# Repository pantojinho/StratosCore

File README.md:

# StratosCore

StratosCore is an open-source portable field, aviation, meteorological, navigation and radio computer based on the **ESP32-S3-WROOM-1-N16R8**.

## Current status

**Astra has assumed full technical leadership of Rev A (2026-09-24).** Astra owns engineering closure, candidate refinement, review and integration; Claude, Hermes, Sol and other AI agents execute bounded delegated tasks. See [Astra project control and agent handover](docs/ASTRA_PROJECT_CONTROL.md) for current responsibilities, received evidence and next actions. Final baseline implementation and manufacturing remain gated.

| Complete | In progress | Externally blocked |
| --- | --- | --- |
| Product baseline and licensing | Validate prepared three-line display support and GNSS passive RF proposals | Display controlled power/FPC drawing, C1 samples and connector confirmation |
| MAX-M10S decision and independently reviewed footprint geometry | Close complete 2S charger/protection/VBUS application | Qualified electrical/battery review and fault tests |
| Two removable 21700 cells in 2S decision | Accept exact cells/holder and state estimation; prove the 8 h primary-use target | RF performance and runtime measurements need prototypes |
| ESP32 compute sheet and GPIO allocation | Sensor CAD, LoRa/ADS-B RF, stackup and mechanical dummy | Final factory stack confirmation |
| Exact candidates for RP2040 support, microSD, audio, USB-C, expansion, buttons, rails and RF interconnects | Assembler approvals, mechanical fit, off-state review and application tests | Independent final schematic/layout and bring-up review |
| Manufacturer-derived dimensions for W25Q, TPD, ICM/MMC/BMP, ABM8, U.FL and DM3 electrical/mechanical envelope | RF return paths, enclosure access and prototype qualification | PCBA assembler stencil/mask confirmation |
| KiCad hierarchy; latest ERC: zero violations | Orderable BOM and manufacturing inputs | |
| ADS-B host models: 24 tests passing | UART/PIO/DMA implementation and sustained-link bench proof | |

The **reviewed baseline** (`hardware/`) has no finished schematic, PCB layout, prototype or manufacturing package yet. A complete **comparison candidate** (schematic + routed PCB + 3D with the display) now exists in [`candidates/claude-oneshot-revA/`](candidates/claude-oneshot-revA/README.md) — see [below](#claude-one-shot-candidate-schematic--pcb--3d). It is **not for manufacture** and does not close any gate. Do not order boards from the current repository. See [project status](docs/PROJECT_STATUS.md) for the complete gate list.

## Claude one-shot candidate (schematic + PCB + 3D)

Generated 2026-09-23 at the owner's request, for side-by-side comparison with the Astra pass. Status at a glance:

| Item | Status |
| --- | --- |
| Schematic | Complete: root + 11 sheets, every Rev A block; unverified values are literally `TBD` |
| PCB | 60 x 84 mm, 4 layers, 277 parts, routed; **11 connections left for manual finish** (2 LoRa RF stubs, SHT40 SDA/3V3, 1 decoupling cap, 6 GND pour fragments) |
| Checks (KiCad 10.0.6) | ERC 1 reviewed error; DRC 1 reviewed error (ESP32 antenna-clearance courtyard); schematic <-> PCB parity 0 |
| 3D | Board with display, 2S 21700 cells and holder; printed two-part enclosure concept |
| Blocking gates | O05 battery safety (qualified human review), display controlled drawing/samples, LoRa matching values, ADS-B threshold, assembler approvals |
| Findings for the baseline | 2 footprint blockers (MMC5983MA, BMP581 pad centres), 2 wrong packages (TXU0202, TPS259474L), connector orientation and GPIO gaps — see [ISSUES.md](candidates/claude-oneshot-revA/docs/ISSUES.md) |

| Front (display) | Back (2S 21700 cells) | Printed enclosure concept |
| --- | --- | --- |
|  |  |  |

| PCB top (display removed) | PCB bottom | Copper (F/In2/B) |
| --- | --- | --- |
|  |  |  |

Schematic sheets (click to enlarge; full vector PDF: [schematic.pdf](candidates/claude-oneshot-revA/docs/schematic.pdf)):

| | | |
| --- | --- | --- |
|  Root |  01 USB-C input |  02 2S battery/charger |
|  03 Rails |  04 ESP32 / control |  05 Display / touch |
|  06 Sensors |  07 GNSS |  08 LoRa |
|  09 ADS-B / RP2040 |  10 microSD / audio |  11 Mechanical |

### Open it in KiCad

1. Download the repository (GitHub **Code -> Download ZIP**, or `git clone`) and install **KiCad 10** (the project uses the KiCad 10 library variables).
2. Open [`candidates/claude-oneshot-revA/kicad/StratosCore_Claude.kicad_pro`](candidates/claude-oneshot-revA/kicad/). Project symbols, footprints and 3D models are local to that folder (`libs/`), so no library setup is needed.
3. Schematic: open the root sheet and double-click a sheet box. PCB: open the board and press **Alt+3** for the 3D viewer (the display and the cells appear in 3D).
4. STEP files for FreeCAD, Fusion or any other CAD are in [`candidates/claude-oneshot-revA/outputs/StratosCore_Claude_3D_STEP.zip`](candidates/claude-oneshot-revA/outputs/StratosCore_Claude_3D_STEP.zip): the board with its display and cells, the full assembly with the enclosure, and the two enclosure parts.

| Folder | What to open |
| --- | --- |
| `candidates/claude-oneshot-revA/kicad/` | KiCad project (`.kicad_pro`, root and sheet `.kicad_sch`, `.kicad_pcb`, local libraries) |
| `candidates/claude-oneshot-revA/docs/` | `schematic.pdf`, `ISSUES.md` (findings and open gates) |
| `candidates/claude-oneshot-revA/outputs/` | STEP zip, renders, layer PDF, BOM, DRC summary, netlist |
| `candidates/claude-oneshot-revA/mech/` | Enclosure STEP parts |
| `candidates/claude-oneshot-revA/images/` | The images above |
| `candidates/claude-oneshot-revA/tools/` | Scripts that regenerate everything |

The owner set a five-unit target of at most BRL 200 per assembled PCB **including display/touch**, excluding locally bought cells and enclosure, freight and taxes. This is a hobby prototype for desk, car and protected but unpressurized aircraft-cabin use, with experimental drone, model-aircraft, balloon, ultralight, hang-glider and paramotor applications to assess separately. About 10,000 ft is the realistic altitude case; 30,000 ft is exploratory, not a guaranteed barometric limit. The BMP581 remains an indicative backup sensor, and the 8 h minimum target on two 21700 cells remains. The five boards will be programmed and tested locally through USB-C. Cost, runtime and flight performance are not yet verified.

## Rev A baseline

| Block | Baseline |
| --- | --- |
| Compute | ESP32-S3-WROOM-1-N16R8; 16 MB Flash, 8 MB PSRAM; Wi-Fi/BLE and module PCB antenna |
| User interface | 2.8-inch IPS 320 x 240 with capacitive touch; portrait/landscape; two physical buttons |
| GNSS | u-blox MAX-M10S-00B, selected for documented airborne modes to 80 km |
| Motion/environment | ICM-42688-P, MMC5983MA, BMP581 and SHT40-AD1B-R2 |
| LoRa | SX1262 directly integrated, 915 MHz class hardware, SPI and PCB U.FL; regional TX configuration required |
| ADS-B | Independent 1090 MHz receive chain with RP2040 timing processor |
| Logging/audio | Mandatory microSD and provision for an optional digital MEMS microphone |
| Power | USB-C target; two removable matched 21700 cells in 2S; one balanced charger and common protection direction |
| Expansion | 3V3, GND, I2C, SPI with separate CS, UART and GPIO/IRQ |
| Construction | Four-layer PCB; 84 x 60 mm planning outline; approximately 88 x 64 x 37 mm printed enclosure starting envelope |

Potential uses include flight/vario instruments, traffic visualization, balloon experiments, weather stations, trackers, LoRa/MeshCore experiments and portable logging. This experimental platform is not a certified aviation instrument, collision-avoidance system or cockpit voice recorder.

## Start here

1. [Project status: completed work and remaining gates](docs/PROJECT_STATUS.md)
2. [Astra-led engineering workboard](docs/PRE_ASTRA_WORKBOARD.md)
3. [Multi-agent swarm protocol and master prompt](docs/SWARM_PROTOCOL.md)
4. [Engineering documentation index](docs/README.md)
5. [Locked decisions and accepted proposals](docs/DECISIONS.md)
6. [Open engineering questions](docs/OPEN_QUESTIONS.md)

[Astra final KiCad handoff](docs/ASTRA_HANDOFF.md) is intentionally marked **NOT READY**. It is not the current work queue.

## Repository layout

```text
StratosCore/
|-- AGENTS.md          Engineering and review rules
|-- README.md          Public project status and entry points
|-- docs/              Status, decisions and subsystem specifications
|-- bom/               Preliminary planning BOM; not orderable yet
|-- hardware/          KiCad project and primary-source index
|-- candidates/        Out-of-baseline design candidates (Claude one-shot: schematic, PCB, 3D)
|-- mechanical/        Enclosure and fit-study workspace
|-- manufacturing/     Release and production-test placeholders
|-- firmware/          Hardware-interface fixtures and future firmware
|-- references/        Read-only research and reuse/license records
`-- LICENSES/          Official license texts and scope
```

## Manufacturing path

The target is four-layer PCB fabrication and automated assembly at JLCPCB or a comparable Chinese PCBA supplier. Release requires an independently reviewed schematic and layout, clean ERC/DRC, confirmed stackup, exact orderable BOM, CPL, Gerbers/drill files, assembly drawings and a programming/production-test procedure. The owner must explicitly accept the manufacturing release before ordering.

## Licensing

Original hardware, mechanical designs and hardware engineering documentation use **CERN-OHL-P-2.0**. Original firmware and its software documentation use **MIT**. See [license scope and provenance](LICENSES/README.md). Third-party work retains its own terms.

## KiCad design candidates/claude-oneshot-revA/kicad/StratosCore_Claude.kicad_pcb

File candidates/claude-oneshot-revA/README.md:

# StratosCore Rev A — Claude one-shot candidate (schematic + PCB + 3D)

> **Status: CANDIDATE FOR COMPARISON — NOT FOR MANUFACTURE, NOT A BASELINE.**
>
> **2026-09-24 project control:** Astra has assumed full technical leadership, review and integration. Claude, Hermes, Sol and other agents execute bounded delegated tasks. See [Astra project control and handover](../../docs/ASTRA_PROJECT_CONTROL.md) for received results, discrepancies and T1–T8. Candidate GPIO/mask decisions remain subject to implementation and validation; root safety, budget and release gates remain in force.
> Produced 2026-09-23 at the owner's explicit request ("1 shot" schematic, PCB and 3D with the display) to be compared with the GPT Astra pass. `docs/ASTRA_HANDOFF.md` is still **NOT READY**; nothing here closes a gate in `docs/PROJECT_STATUS.md`. Battery safety (O05) needs a qualified human reviewer — **do not energize this design with cells.** The repository baseline in `hardware/` is untouched.
>
> **2026-09-23 refinement:** evidence-backed corrections were applied inside this folder (TXU0202 exact DCU land, TPS259474L RPW stencil/fab, ICM-42688-P pin 9 to GND, U1/J5 courtyard, duplicate vias, BMP581 under-body SCL route, SHT40 SDA, 3V3 fragments, three GND islands, silkscreen). See [docs/REFINEMENT_2026_09_23.md](docs/REFINEMENT_2026_09_23.md) for evidence, before/after reports and the blockers that remain.
>
> **2026-09-23 GND stitch (Hermes, evening):** three floating GND pads (U2 USB-ESD, U3.8 eFuse, U24.2 TXU0202) were reported connected to the In1 plane — `unconnected` down to 2 (LoRa TBD items). U7 land updated to RGT0016C. See [docs/GND_STITCH_2026_09_23.md](docs/GND_STITCH_2026_09_23.md). The 10 U3 clearance findings remain electrical defects requiring resolution, not cosmetic findings or fabrication acceptance.

| Front (display) | Back (2S 21700 cells) | PCB top | Enclosure concept |
| --- | --- | --- | --- |
|  |  |  |  |

All 12 schematic sheets are in [`images/`](images/) as PNG (`schematic_00_root.png` ... `schematic_11_mechanical.png`) and in [`docs/schematic.pdf`](docs/schematic.pdf).

## Open it in KiCad

1. Install **KiCad 10** and download/clone the repository.
2. Open `kicad/StratosCore_Claude.kicad_pro`. Symbols, footprints and 3D models used by the project live in `kicad/libs/` (`SC.kicad_sym`, `SC.pretty`, `SC.3dshapes`) and are referenced through `${KIPRJMOD}`; standard KiCad parts come from the KiCad 10 install.
3. Schematic: root sheet -> double-click a sheet box. PCB: open the board, **Alt+3** for the 3D view (display envelope 5 mm above the board, 2S cells below).
4. Other CAD tools: unzip `outputs/StratosCore_Claude_3D_STEP.zip` (board + display + cells, full assembly with enclosure, enclosure parts).

## What is in this folder

| Path | Content |
| --- | --- |
| `kicad/StratosCore_Claude.kicad_pro/.kicad_sch/.kicad_pcb` | KiCad 10.0.6 project: root + 11 hierarchical sheets, 4-layer 60 x 84 mm board |
| `kicad/libs/SC.kicad_sym`, `SC.pretty`, `SC.3dshapes` | Project symbols (datasheet pin tables), footprints (repo candidates + generated/corrected ones), STEP envelopes |
| `kicad/reports/` | Current ERC/DRC JSON and netlist, dated `before_2026-09-23/` and `after_2026-09-23/` sets with net/pad reconciliation, unassigned-pin report (pre-refinement) |
| `docs/schematic.pdf` | Schematic, 12 pages |
| `docs/ISSUES.md` | **Findings against the repo baseline (incl. 2 footprint blockers), open gates, layout limitations** |
| `docs/REFINEMENT_2026_09_23.md` | Refinement record: preflight, evidence per correction, before/after checks, dispositions, blockers |
| `outputs/` | Renders (top/bottom/iso), `StratosCore_Claude_3D_STEP.zip` (board STEP with display + 2S cells, full assembly STEP with the enclosure, enclosure parts), assembly SVG views, layer PDF, BOM, review-only positions, DRC summary |
| `mech/` | Printed enclosure concept (front bezel with display window, back shell) |
| `images/` | README images: 3D renders, enclosure views, copper layers, all schematic sheets |
| `tools/` | Reproducible generators: `design.py` (circuit), `build_sch.py`, `build_pcb.py`, `models3d.py`, `assemble.py`, `export.py` |

## Design summary

- **Compute:** ESP32-S3-WROOM-1-N16R8, GPIO map exactly as `docs/INTERFACE_GPIO_MAP.md`; antenna at the left board edge.
- **Power:** USB-C (USB4105) -> TPD4E05U06 -> TPS259474L eFuse (PWR-02 values) -> BQ25887 balanced 2S charger (TI Fig. 69 values, fail-safe CD) -> removable 2S 21700 holder -> S-8252-family protection placeholder (O05) -> TPS62130A 3V3_MAIN; TPS7A2030 quiet 3.0 V (ADS-B), TPS7A2018 1.8 V; three TPS22918 switched domains (SD, ADS-B digital, audio).
- **Display:** Orient AFY240320A1-2.8INTH-C1 on XF3M-4015/0615 FPC connectors, SN74AXC4T245 3.3->1.8 V write-only 3-line SPI, SN74LVC1G07 reset, TPS61169 backlight (2.21 ohm, ~92 mA). Modelled 5 mm above the PCB on a printed frame.
- **Sensors:** ICM-42688-P, MMC5983MA, BMP581 (vent edge, no copper under body), SHT40 on a slotted thermal tab.
- **Radios:** MAX-M10S-00B GNSS (passive antenna U.FL + TPD1E0B04), SX1262 + PE4259 (topology only, all RF values TBD), ADS-B chain BLB01 -> TA2003A -> BLB01 -> TA2003A -> ADL5513 -> MCP6566 -> RP2040 (+ W25Q128JVSIQ, ABM8-272-T3).
- **Other:** DM3AT microSD on switched 3V3_SD, T5838 PDM mic via TXU0202 on 1V8_AUDIO_SW, TCA9535 slow control, JST GH 12-pin expansion (board back), two SKSCLCE010 side buttons, test pads for rails/SWD/RUN/USB_BOOT/buses.

Every value that is not closed by a cited source is literally `TBD` in the schematic (value or `Status` field); see the BOM `Status` column.

## Verification status (KiCad 10.0.6; ERC/DRC rechecked 2026-09-24)

Records: [docs/REFINEMENT_2026_09_23.md](docs/REFINEMENT_2026_09_23.md) and the follow-up notes in [docs/review_notes/](docs/review_notes/). KiCad reports at most 199 items per violation type, so 199 is a lower bound.

[Astra's September 24 review](../../docs/ASTRA_AGENT_REVIEW_2026_09_24.md) independently reran ERC/DRC with zone refill. Other dimensional, physical and functional claims below retain their original evidence dates and limits.

| Check | Result |
| --- | --- |
| ERC (12 sheets) | 1 error (intended: BMP581 `INT` strapped to GND with `INT_CONFIG.int_en` kept disabled, Bosch DS004-13 Table 28/§6.2) + 5 warnings (intended GND straps; flattened `2N7002` symbol) |
| Schematic <-> PCB parity / net-pad reconciliation | **0** / 970 pins, 0 mismatches (correspondence only) |
| GND copper | one connected group (U2 USB ESD, U3 eFuse, U24, U7 buck EP and the sensor islands are now stitched) |
| DRC errors | **209 reported: 10 clearance + 199 mask bridges**, plus 2 unconnected items listed separately. Mask count is a lower bound; clearance and mask/routing defects remain open. See [Astra's fresh review](../../docs/ASTRA_AGENT_REVIEW_2026_09_24.md) and [assembler note](docs/review_notes/ASSEMBLER_MASK_AND_COST_SNAPSHOT.md) |
| DRC warnings | 118 silkscreen (cosmetic) + 1 dangling LoRa RF stub |
| Unconnected | **2**: SX1262 `LORA_RFO`/`LORA_RFI_P`, the intended RF blocker ([E449 reference values](docs/review_notes/SX1262_E449_REFERENCE_VALUES.md) found; the `08_lora` topology must first be redrawn to E449) |
| ESP32 / USB-C / buttons | All 41 module pads traced to Espressif Table 3-1 and the GPIO map; USB-C on the bottom (PWR) edge and buttons on the right edge, both facing out — see [audit](docs/review_notes/ESP32_USB_BUTTONS_AUDIT.md) for the open antenna/display and enclosure items |

Routing: Freerouting 2.4.1 (40 passes) on an engineering-anchored placement (`tools/build_pcb.py`), then this package's A* clean-up router (`tools/gridroute.py`), automated GND via stitching (`tools/finalize.py`) and polish (`tools/polish.py`); `tools/route_all.py` chains the stages. **A low DRC count proves CAD consistency only — not RF, power, battery-safety, thermal, EMI or manufacturability.** RF paths and USB were not given controlled-impedance geometry.

## How to regenerate

> The generators below produced the original one-shot. They do **not** include the 2026-09-23 refinement; re-running them would revert it. The KiCad files are now the source of truth; the refinement scripts are `tools/refine_2026_09_23_*.py` and `tools/fp_rpw_dcu_2026_09_23.py`. `outputs/StratosCore_Claude_3D_STEP.zip` is the ORIGINAL pre-refinement export (kept for history). Current-state models: `outputs/StratosCore_Claude_board_2026-09-23.step(.zip)` (board STEP, post-GND-stitch) and `outputs/positions_REVIEW_ONLY.csv` (re-exported from the current board).

```bash
"C:/Program Files/KiCad/10.0/bin/python.exe" tools/build_sch.py
```
```bash
"C:/Program Files/KiCad/10.0/bin/python.exe" tools/build_pcb.py
```
```bash
<python-with-cadquery> tools/models3d.py
```
```bash
"C:/Program Files/KiCad/10.0/bin/python.exe" tools/route_all.py --passes 40
```
```bash
"C:/Program Files/KiCad/10.0/bin/python.exe" tools/export.py
```
```bash
<python-with-cadquery> tools/assemble.py
```

STEP outputs are written to `outputs/` and committed zipped (`StratosCore_Claude_3D_STEP.zip`). Routing uses Freerouting 2.4.1 (`freerouting-2.4.1.jar`, GPL-3.0, run as an external tool only — not bundled) on an Eclipse Temurin 25 JRE; set `STRATOS_TOOLS` to the folder holding both.

## Tool provenance and licensing

- Hardware files: CERN-OHL-P-2.0 (repository policy). Generator scripts: MIT (tooling, not firmware).
- `tools/schgen.py` adapts ideas (coordinate transform, `extends` flattening, stub/label drawing) from [pantojinho/hermes-kicad-pcb](https://github.com/pantojinho/hermes-kicad-pcb) `sch_gen.py`, MIT, commit `c87e8d4`; the KiCad pitfalls list and board-from-netlist flow of `sch_to_board.py` informed `build_pcb.py`. [aklofas/kicad-happy](https://github.com/aklofas/kicad-happy) (MIT) was consulted as the review-skill reference; none of its code is included.
- KiCad library symbols/footprints/3D models are used under the KiCad libraries' license (CC-BY-SA 4.0 with the design exception).
- Datasheet facts used for new symbols/footprints are cited in each symbol `Datasheet` field / footprint `descr` and in `docs/ISSUES.md`.

## Suggested Astra comparison checklist

1. Did the other pass catch **A13 (MMC5983MA pad centres)** and **A14 (BMP581 pad centres)**, **A1/A2 (TXU0202 / TPS259474L wrong packages)** and **A3 (BM12B is vertical)**?
2. How were the GPIO gaps (A5-A8: EXP_CS, SX1262 NRESET, RP2040 RUN, touch reset) resolved?
3. Placement: antenna vs 2S holder (A16), holder vs mounting holes/THT (A15), sensor placement rules (SNS-02), RF chain adjacency.
4. Did it invent LoRa matching values, ADS-B threshold, charger/protection parts or display pin ties, or leave them TBD?
5. Routing quality of RF (GCPW), USB (90 ohm pair), buck/charger hot loops — neither pass should be trusted without hand review.

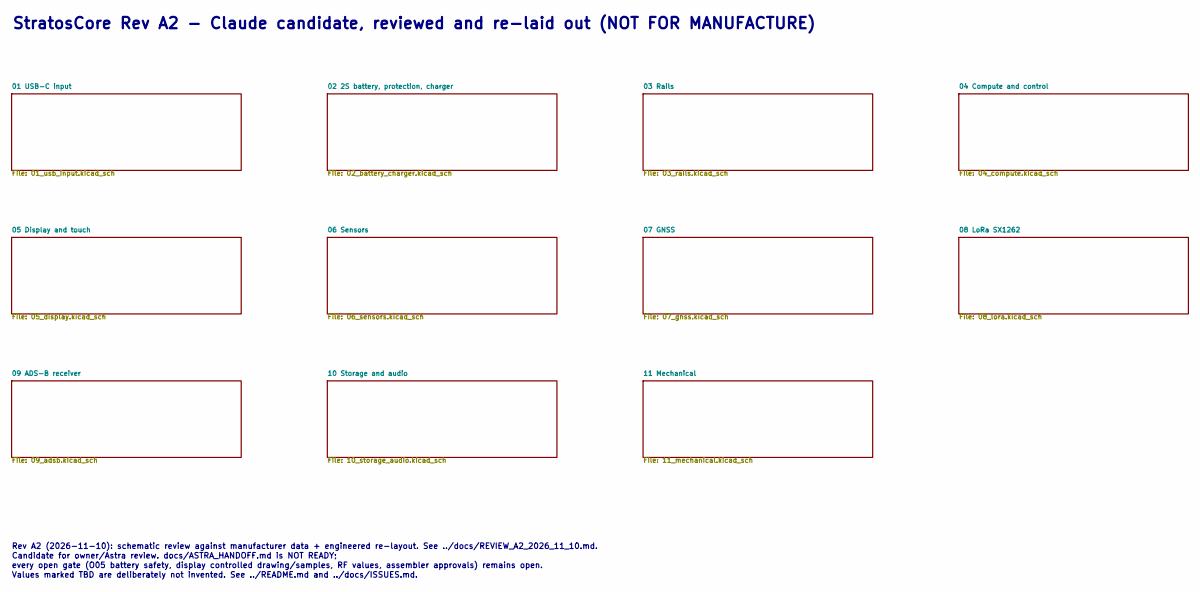
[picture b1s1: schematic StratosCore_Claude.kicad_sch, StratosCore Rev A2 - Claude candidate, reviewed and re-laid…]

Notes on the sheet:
StratosCore Rev A2 - Claude candidate, reviewed and re-laid out (NOT FOR MANUFACTURE)
Rev A2 (2026-11-10): schematic review against manufacturer data + engineered re-layout. See ../docs/REVIEW_A2_2026_11_10.md.
Candidate for owner/Astra review. docs/ASTRA_HANDOFF.md is NOT READY;
every open gate (O05 battery safety, display controlled drawing/samples, RF values, assembler approvals) remains open.
Values marked TBD are deliberately not invented. See ../README.md and ../docs/ISSUES.md.

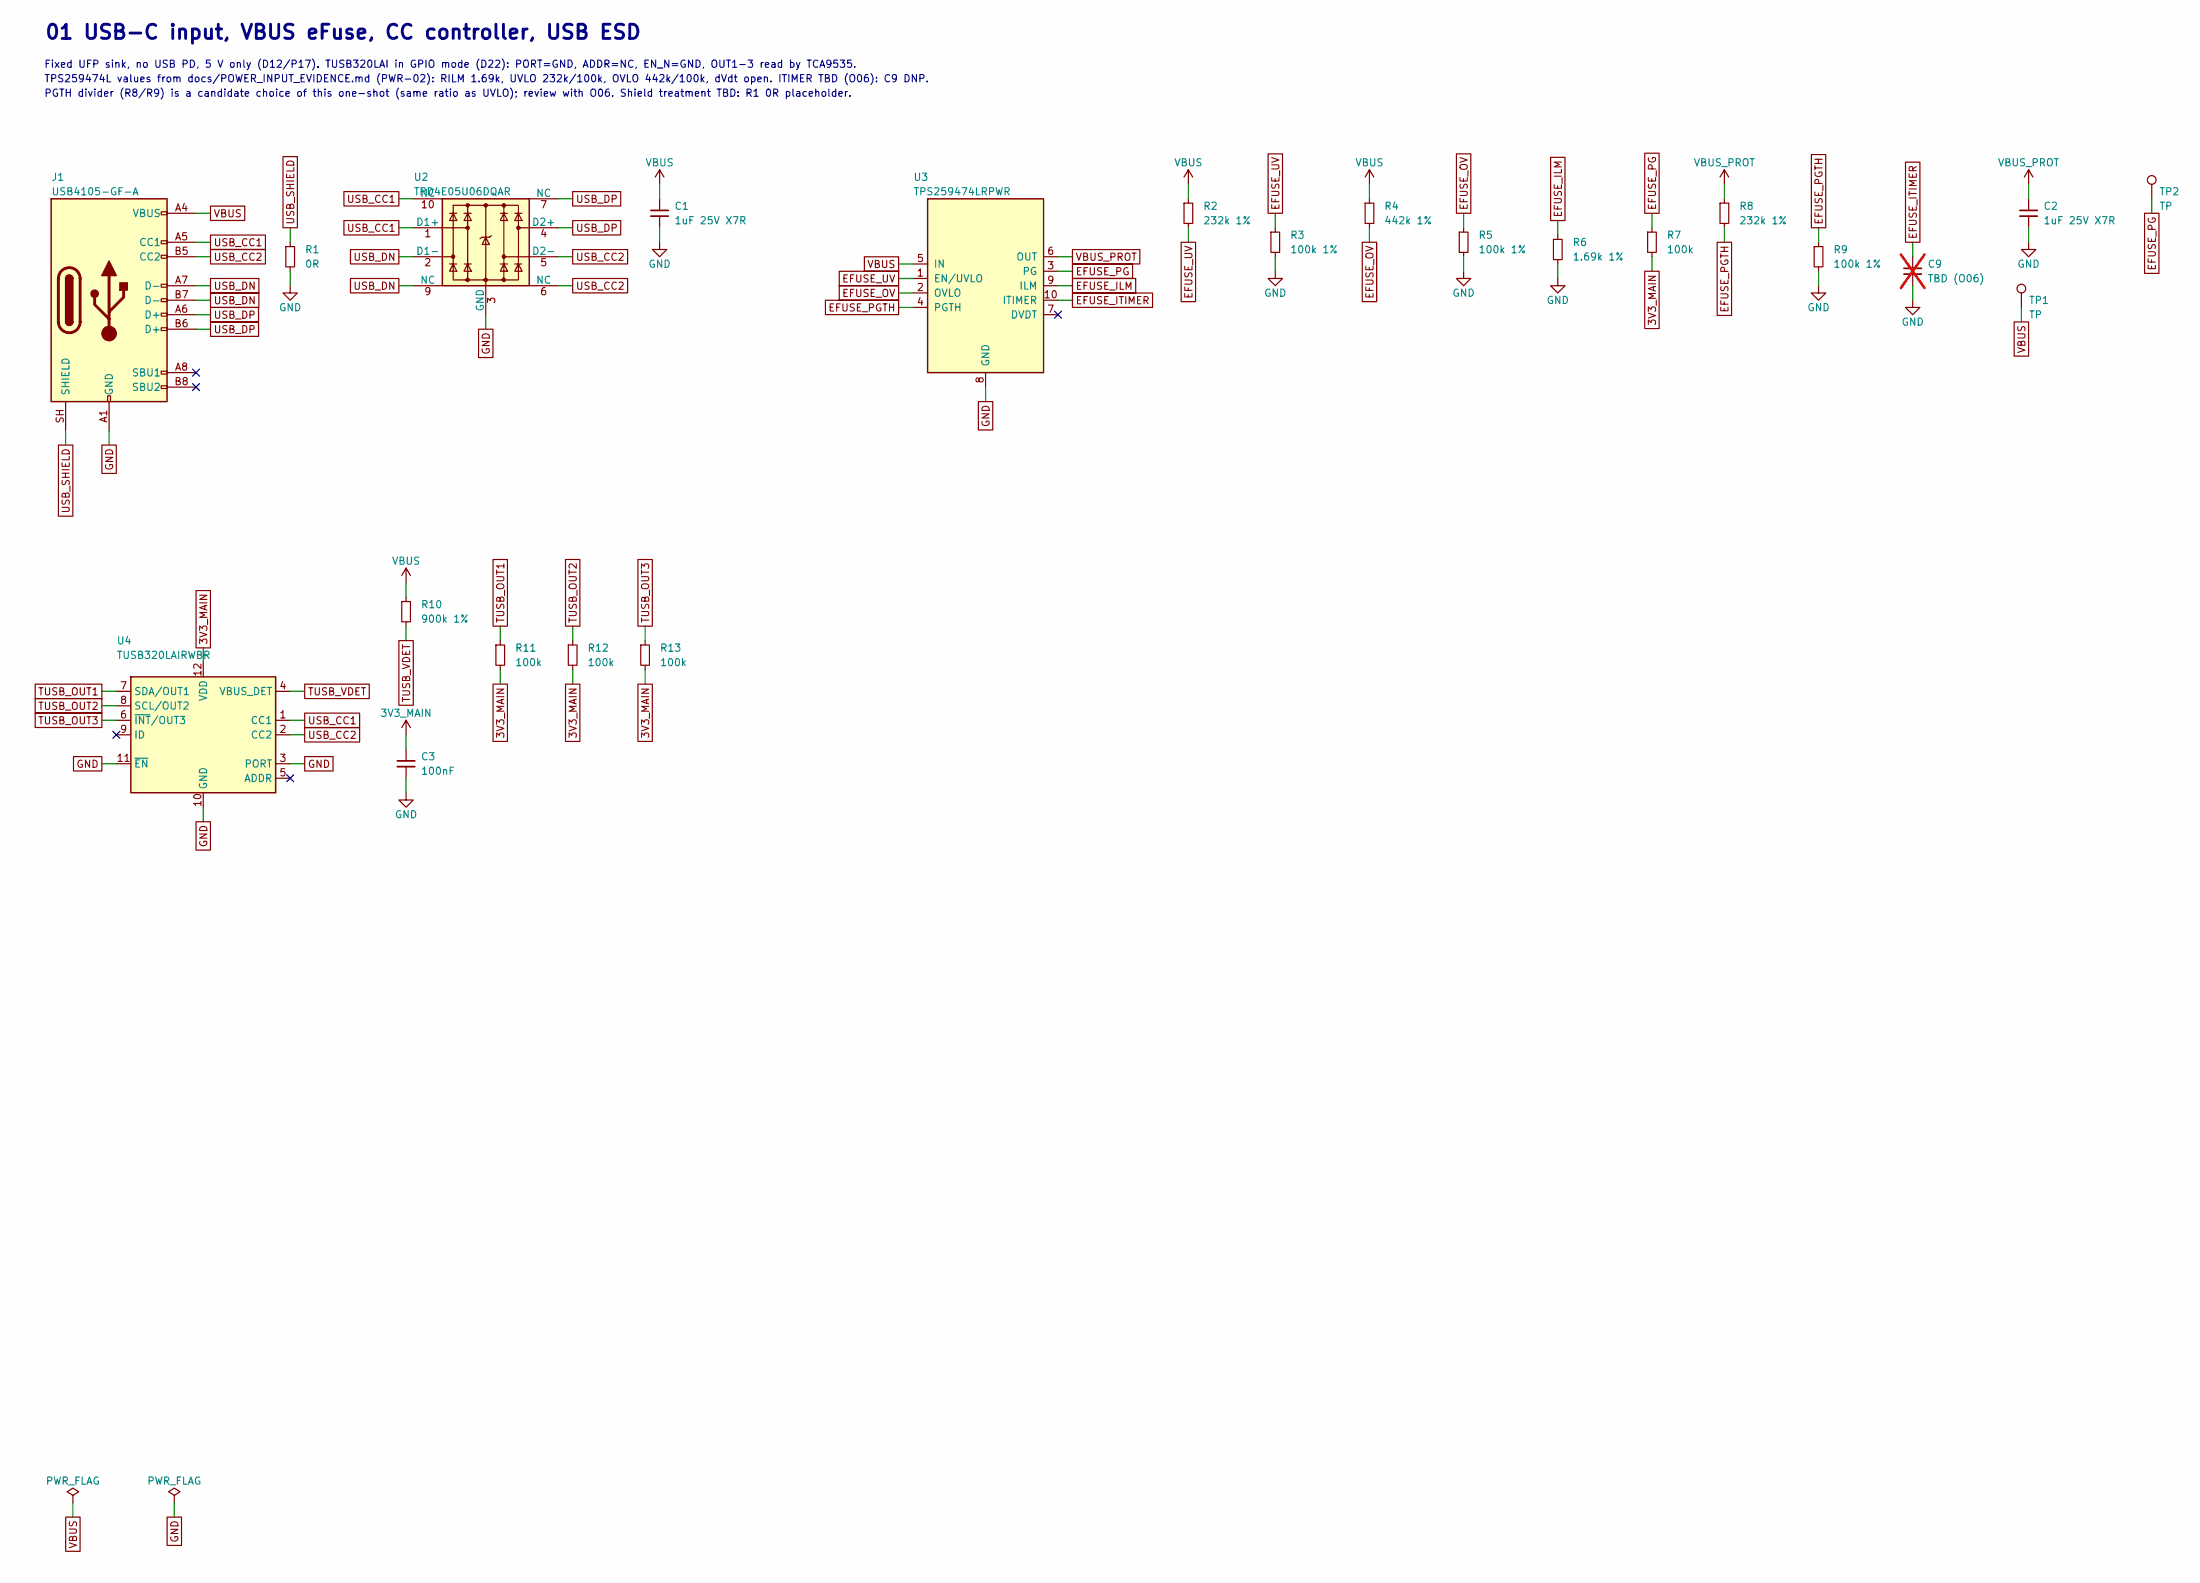
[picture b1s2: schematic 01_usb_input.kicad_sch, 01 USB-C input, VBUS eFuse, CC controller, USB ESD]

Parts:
C1, C2: 1uF 25V X7R; C_0603_1608Metric
C3: 100nF; C_0402_1005Metric
C9: TBD (O06); C_0402_1005Metric; not fitted
J1: USB4105-GF-A; USB_C_Receptacle_GCT_USB4105-xx-A_16P_TopMnt_Horizontal; MPN USB4105-GF-A
R1: 0R; R_0402_1005Metric
R2, R8: 232k 1%; R_0402_1005Metric
R3, R5, R9: 100k 1%; R_0402_1005Metric
R4: 442k 1%; R_0402_1005Metric
R6: 1.69k 1%; R_0402_1005Metric
R7, R11, R12, R13: 100k; R_0402_1005Metric
R10: 900k 1%; R_0402_1005Metric
TP1, TP2: TP; TestPoint_Pad_D1.0mm
U2: TPD4E05U06DQAR; USON-10_2.5x1.0mm_P0.5mm; MPN TPD4E05U06DQARG4
U3: TPS259474LRPWR; TI_RPW0010A_VQFN-HR-10_2x2mm_P0.45mm; MPN TPS259474LRPWR
U4: TUSB320LAIRWBR; TI_RWB0012B_X2QFN-12_1.6x1.6mm_TUSB320LAI; MPN TUSB320LAIRWBR

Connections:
3V3_MAIN: C3.1, R7.2, R11.2, R12.2, R13.2, U4.12 (VDD); also elsewhere on the board
EFUSE_ILM: R6.1, U3.9 (ILM)
EFUSE_ITIMER: C9.1, U3.10 (ITIMER)
EFUSE_OV: R4.2, R5.1, U3.2 (OVLO)
EFUSE_PG: R7.1, TP2.1, U3.3 (PG)
EFUSE_PGTH: R8.2, R9.1, U3.4 (PGTH)
EFUSE_UV: R2.2, R3.1, U3.1 (EN/UVLO)
GND: C1.2, C2.2, C3.2, C9.2, J1.A1 (GND), J1.A12 (GND), J1.B1 (GND), J1.B12 (GND), R1.2, R3.2, R5.2, R6.2, R9.2, U2.3 (GND), U2.8 (GND), U3.8 (GND), U4.3 (PORT), U4.10 (GND), U4.11 (~EN); also elsewhere on the board
TUSB_OUT1: R11.1, U4.7 (SDA/OUT1); also elsewhere on the board
TUSB_OUT2: R12.1, U4.8 (SCL/OUT2); also elsewhere on the board
TUSB_OUT3: R13.1, U4.6 (~INT/OUT3); also elsewhere on the board
TUSB_VDET: R10.2, U4.4 (VBUS_DET)
USB_CC1: J1.A5 (CC1), U2.1 (D1+), U2.10 (NC), U4.1 (CC1)
USB_CC2: J1.B5 (CC2), U2.5 (D2-), U2.6 (NC), U4.2 (CC2)
USB_DN: J1.A7 (D-), J1.B7 (D-), U2.2 (D1-), U2.9 (NC); also elsewhere on the board
USB_DP: J1.A6 (D+), J1.B6 (D+), U2.4 (D2+), U2.7 (NC); also elsewhere on the board
USB_SHIELD: J1.SH (SHIELD), R1.1
VBUS: C1.1, J1.A4 (VBUS), J1.A9 (VBUS), J1.B4 (VBUS), J1.B9 (VBUS), R2.1, R4.1, R10.1, TP1.1, U3.5 (IN)
VBUS_PROT: C2.1, R8.1, U3.6 (OUT); also elsewhere on the board

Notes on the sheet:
01 USB-C input, VBUS eFuse, CC controller, USB ESD
Fixed UFP sink, no USB PD, 5 V only (D12/P17). TUSB320LAI in GPIO mode (D22): PORT=GND, ADDR=NC, EN_N=GND, OUT1-3 read by TCA9535.
TPS259474L values from docs/POWER_INPUT_EVIDENCE.md (PWR-02): RILM 1.69k, UVLO 232k/100k, OVLO 442k/100k, dVdt open. ITIMER TBD (O06): C9 DNP.
PGTH divider (R8/R9) is a candidate choice of this one-shot (same ratio as UVLO); review with O06. Shield treatment TBD: R1 0R placeholder.

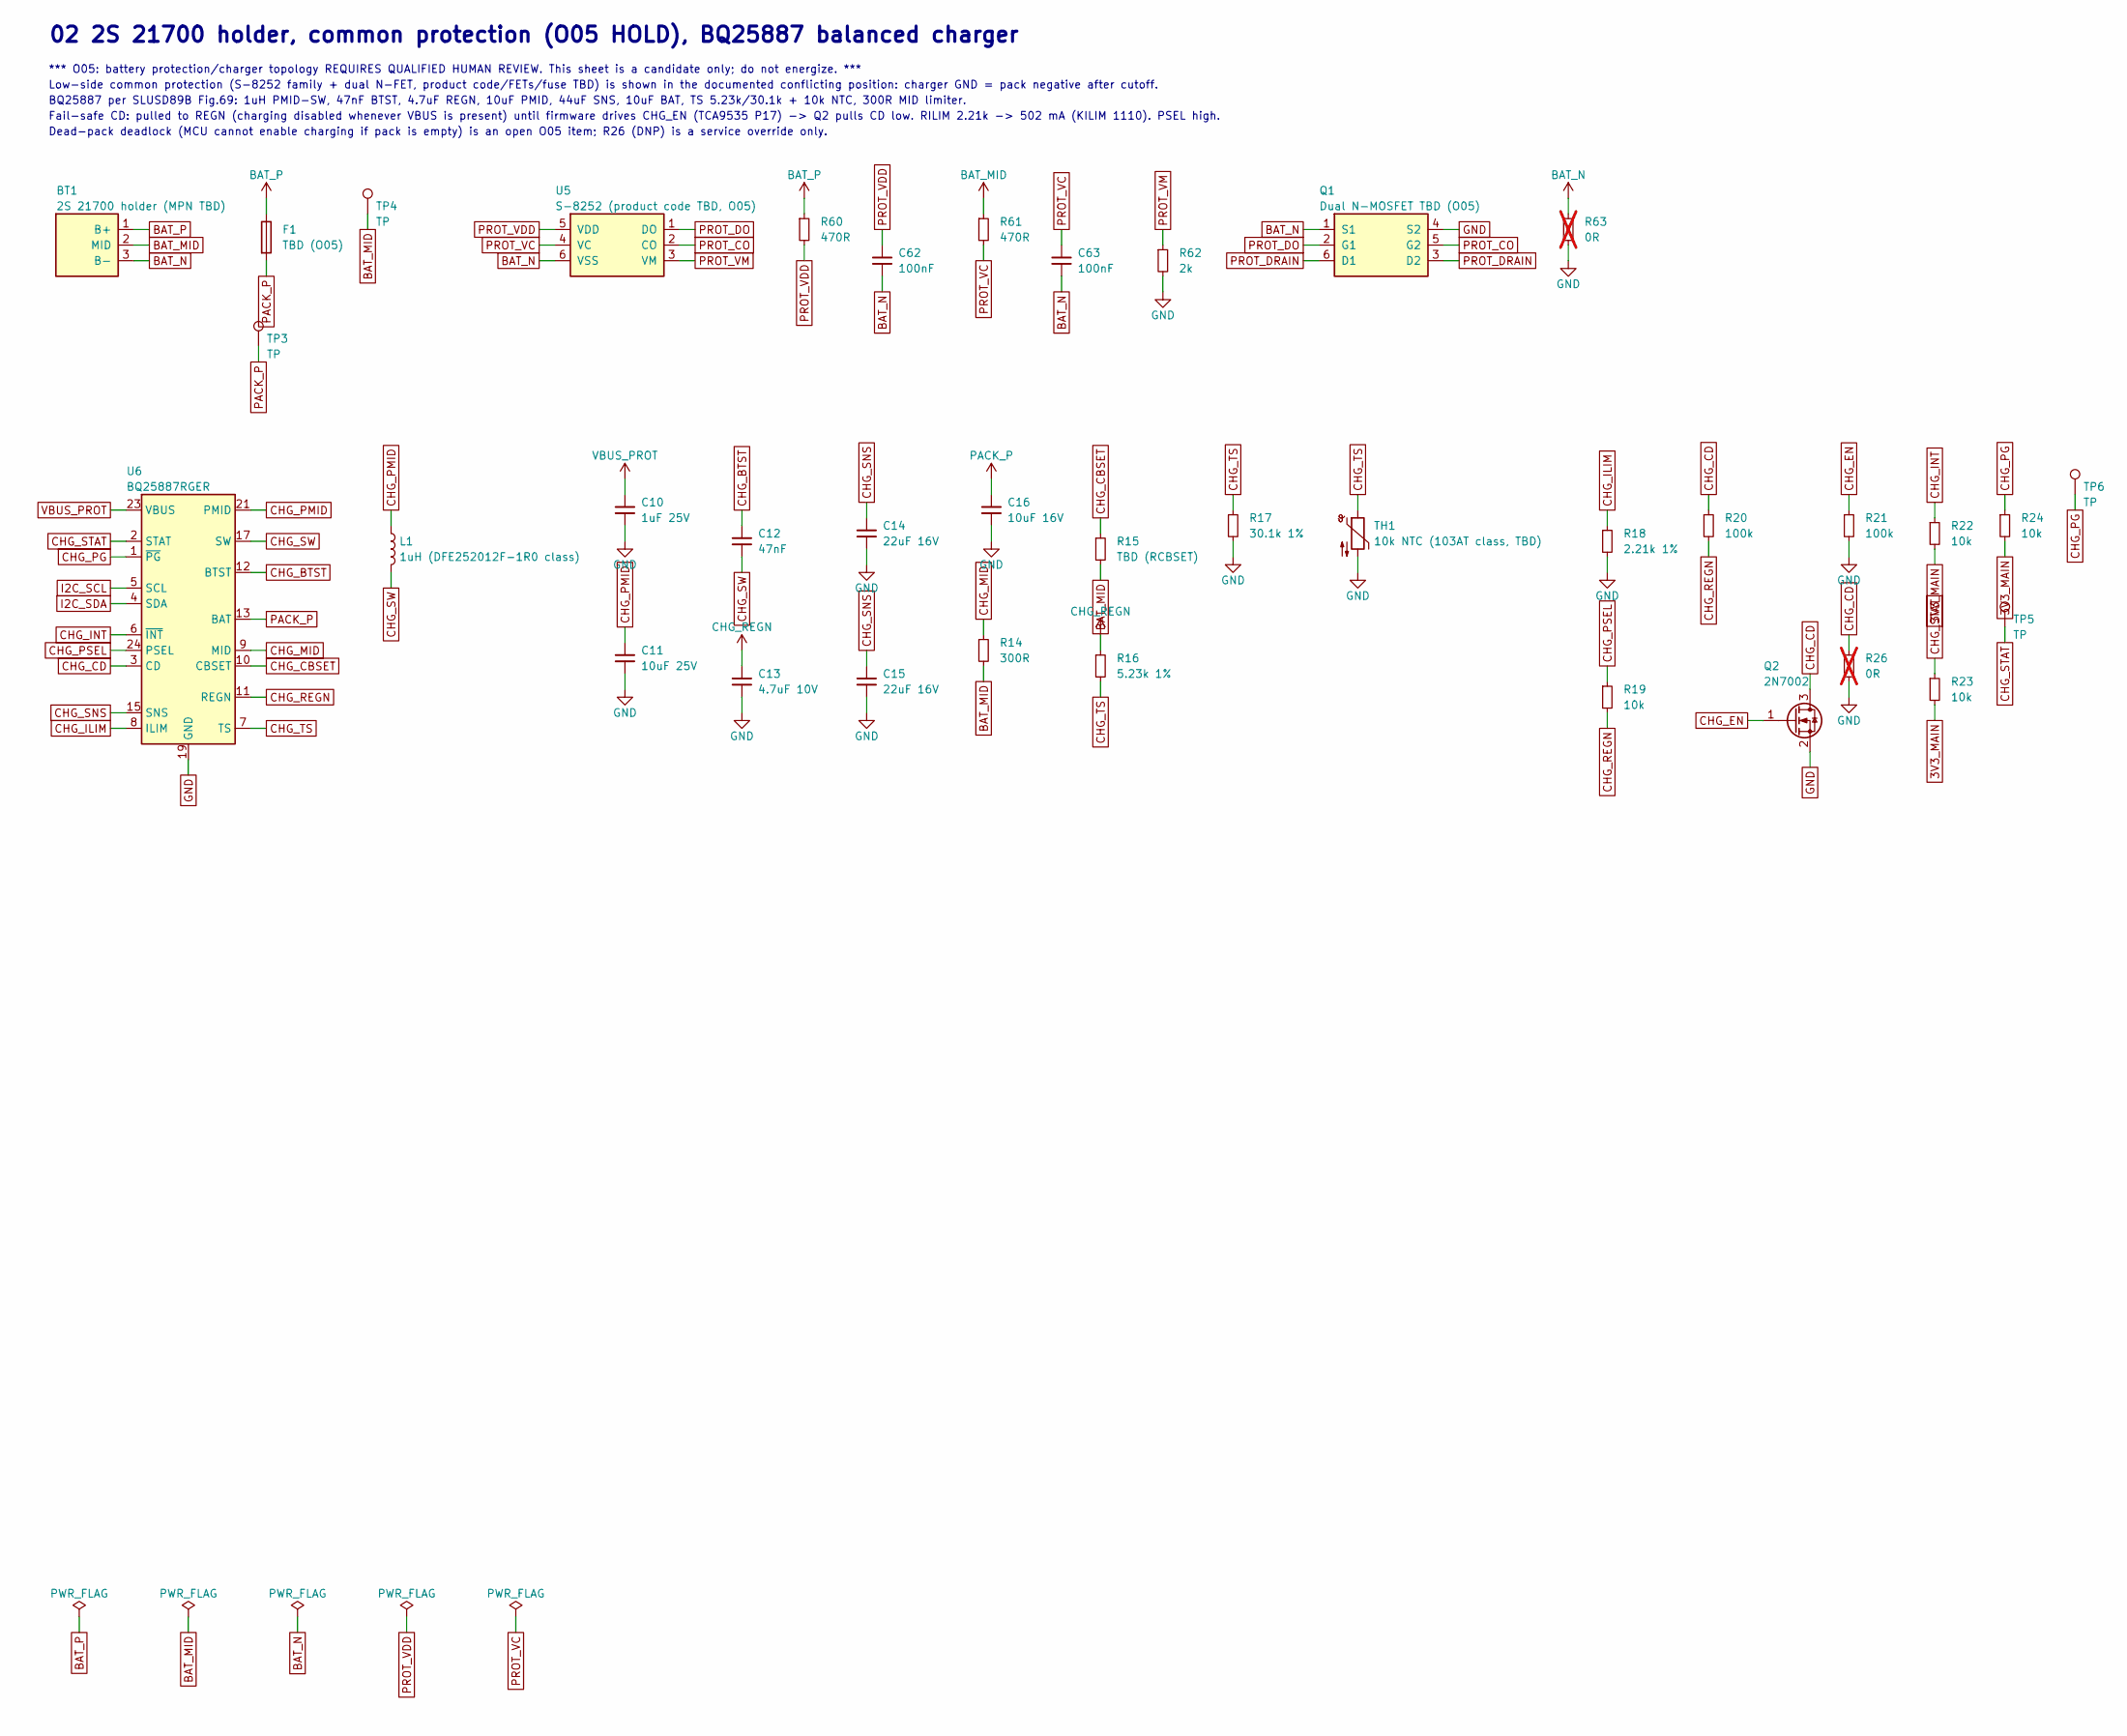
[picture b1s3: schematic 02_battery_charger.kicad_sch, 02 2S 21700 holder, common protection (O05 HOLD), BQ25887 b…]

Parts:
BT1: 2S 21700 holder (MPN TBD); BatteryHolder_2S_21700_TBD; MPN TBD
C10: 1uF 25V; C_0603_1608Metric
C11: 10uF 25V; C_0805_2012Metric
C12: 47nF; C_0402_1005Metric
C13: 4.7uF 10V; C_0603_1608Metric
C14, C15: 22uF 16V; C_0805_2012Metric
C16: 10uF 16V; C_0805_2012Metric
C62, C63: 100nF; C_0402_1005Metric
F1: TBD (O05); Fuse_1206_3216Metric
L1: 1uH (DFE252012F-1R0 class); L_1008_2520Metric
Q1: Dual N-MOSFET TBD (O05); SOT-23-6
Q2: 2N7002; SOT-23
R14: 300R; R_0603_1608Metric
R15: TBD (RCBSET); R_2512_6332Metric
R16: 5.23k 1%; R_0402_1005Metric
R17: 30.1k 1%; R_0402_1005Metric
R18: 2.21k 1%; R_0402_1005Metric
R19, R22, R23, R24: 10k; R_0402_1005Metric
R20, R21: 100k; R_0402_1005Metric
R26: 0R; R_0402_1005Metric; not fitted
R60, R61: 470R; R_0402_1005Metric
R62: 2k; R_0402_1005Metric
R63: 0R; R_1206_3216Metric; not fitted
TH1: 10k NTC (103AT class, TBD); R_0603_1608Metric
TP3, TP4, TP5, TP6: TP; TestPoint_Pad_D1.0mm
U5: S-8252 (product code TBD, O05); SOT-23-6
U6: BQ25887RGER; Texas_RGE0024H_VQFN-24-1EP_4x4mm_P0.5mm_EP2.7x2.7mm; MPN BQ25887RGER

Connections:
3V3_MAIN: R22.2, R23.2, R24.2; also elsewhere on the board
BAT_MID: BT1.2 (MID), R14.2, R15.2, R61.1, TP4.1
BAT_N: BT1.3 (B-), C62.2, C63.2, Q1.1 (S1), R63.1, U5.6 (VSS)
BAT_P: BT1.1 (B+), F1.1, R60.1
CHG_BTST: C12.1, U6.12 (BTST)
CHG_CBSET: R15.1, U6.10 (CBSET)
CHG_CD: Q2.3 (D), R20.1, R26.1, U6.3 (CD)
CHG_EN: Q2.1 (G), R21.1; also elsewhere on the board
CHG_ILIM: R18.1, U6.8 (ILIM)
CHG_INT: R22.1, U6.6 (~INT); also elsewhere on the board
CHG_MID: R14.1, U6.9 (MID)
CHG_PG: R24.1, TP6.1, U6.1 (~PG)
CHG_PMID: C11.1, L1.1, U6.21 (PMID), U6.22 (PMID)
CHG_PSEL: R19.1, U6.24 (PSEL)
CHG_REGN: C13.1, R16.1, R19.2, R20.2, U6.11 (REGN)
CHG_SNS: C14.1, C15.1, U6.15 (SNS), U6.16 (SNS)
CHG_STAT: R23.1, TP5.1, U6.2 (STAT)
CHG_SW: C12.2, L1.2, U6.17 (SW), U6.18 (SW)
CHG_TS: R16.2, R17.1, TH1.1, U6.7 (TS)
GND: C10.2, C11.2, C13.2, C14.2, C15.2, C16.2, Q1.4 (S2), Q2.2 (S), R17.2, R18.2, R21.2, R26.2, R62.2, R63.2, TH1.2, U6.19 (GND), U6.20 (GND), U6.25 (GND); also elsewhere on the board
I2C_SCL: U6.5 (SCL); also elsewhere on the board
I2C_SDA: U6.4 (SDA); also elsewhere on the board
PACK_P: C16.1, F1.2, TP3.1, U6.13 (BAT), U6.14 (BAT); also elsewhere on the board
PROT_CO: Q1.5 (G2), U5.2 (CO)
PROT_DO: Q1.2 (G1), U5.1 (DO)
PROT_DRAIN: Q1.3 (D2), Q1.6 (D1)
PROT_VC: C63.1, R61.2, U5.4 (VC)
PROT_VDD: C62.1, R60.2, U5.5 (VDD)
PROT_VM: R62.1, U5.3 (VM)
VBUS_PROT: C10.1, U6.23 (VBUS); also elsewhere on the board

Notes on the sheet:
02 2S 21700 holder, common protection (O05 HOLD), BQ25887 balanced charger
*** O05: battery protection/charger topology REQUIRES QUALIFIED HUMAN REVIEW. This sheet is a candidate only; do not energize. ***
Low-side common protection (S-8252 family + dual N-FET, product code/FETs/fuse TBD) is shown in the documented conflicting position: charger GND = pack negative after cutoff.
BQ25887 per SLUSD89B Fig.69: 1uH PMID-SW, 47nF BTST, 4.7uF REGN, 10uF PMID, 44uF SNS, 10uF BAT, TS 5.23k/30.1k + 10k NTC, 300R MID limiter.
Fail-safe CD: pulled to REGN (charging disabled whenever VBUS is present) until firmware drives CHG_EN (TCA9535 P17) -> Q2 pulls CD low. RILIM 2.21k -> 502 mA (KILIM 1110). PSEL high.
Dead-pack deadlock (MCU cannot enable charging if pack is empty) is an open O05 item; R26 (DNP) is a service override only.

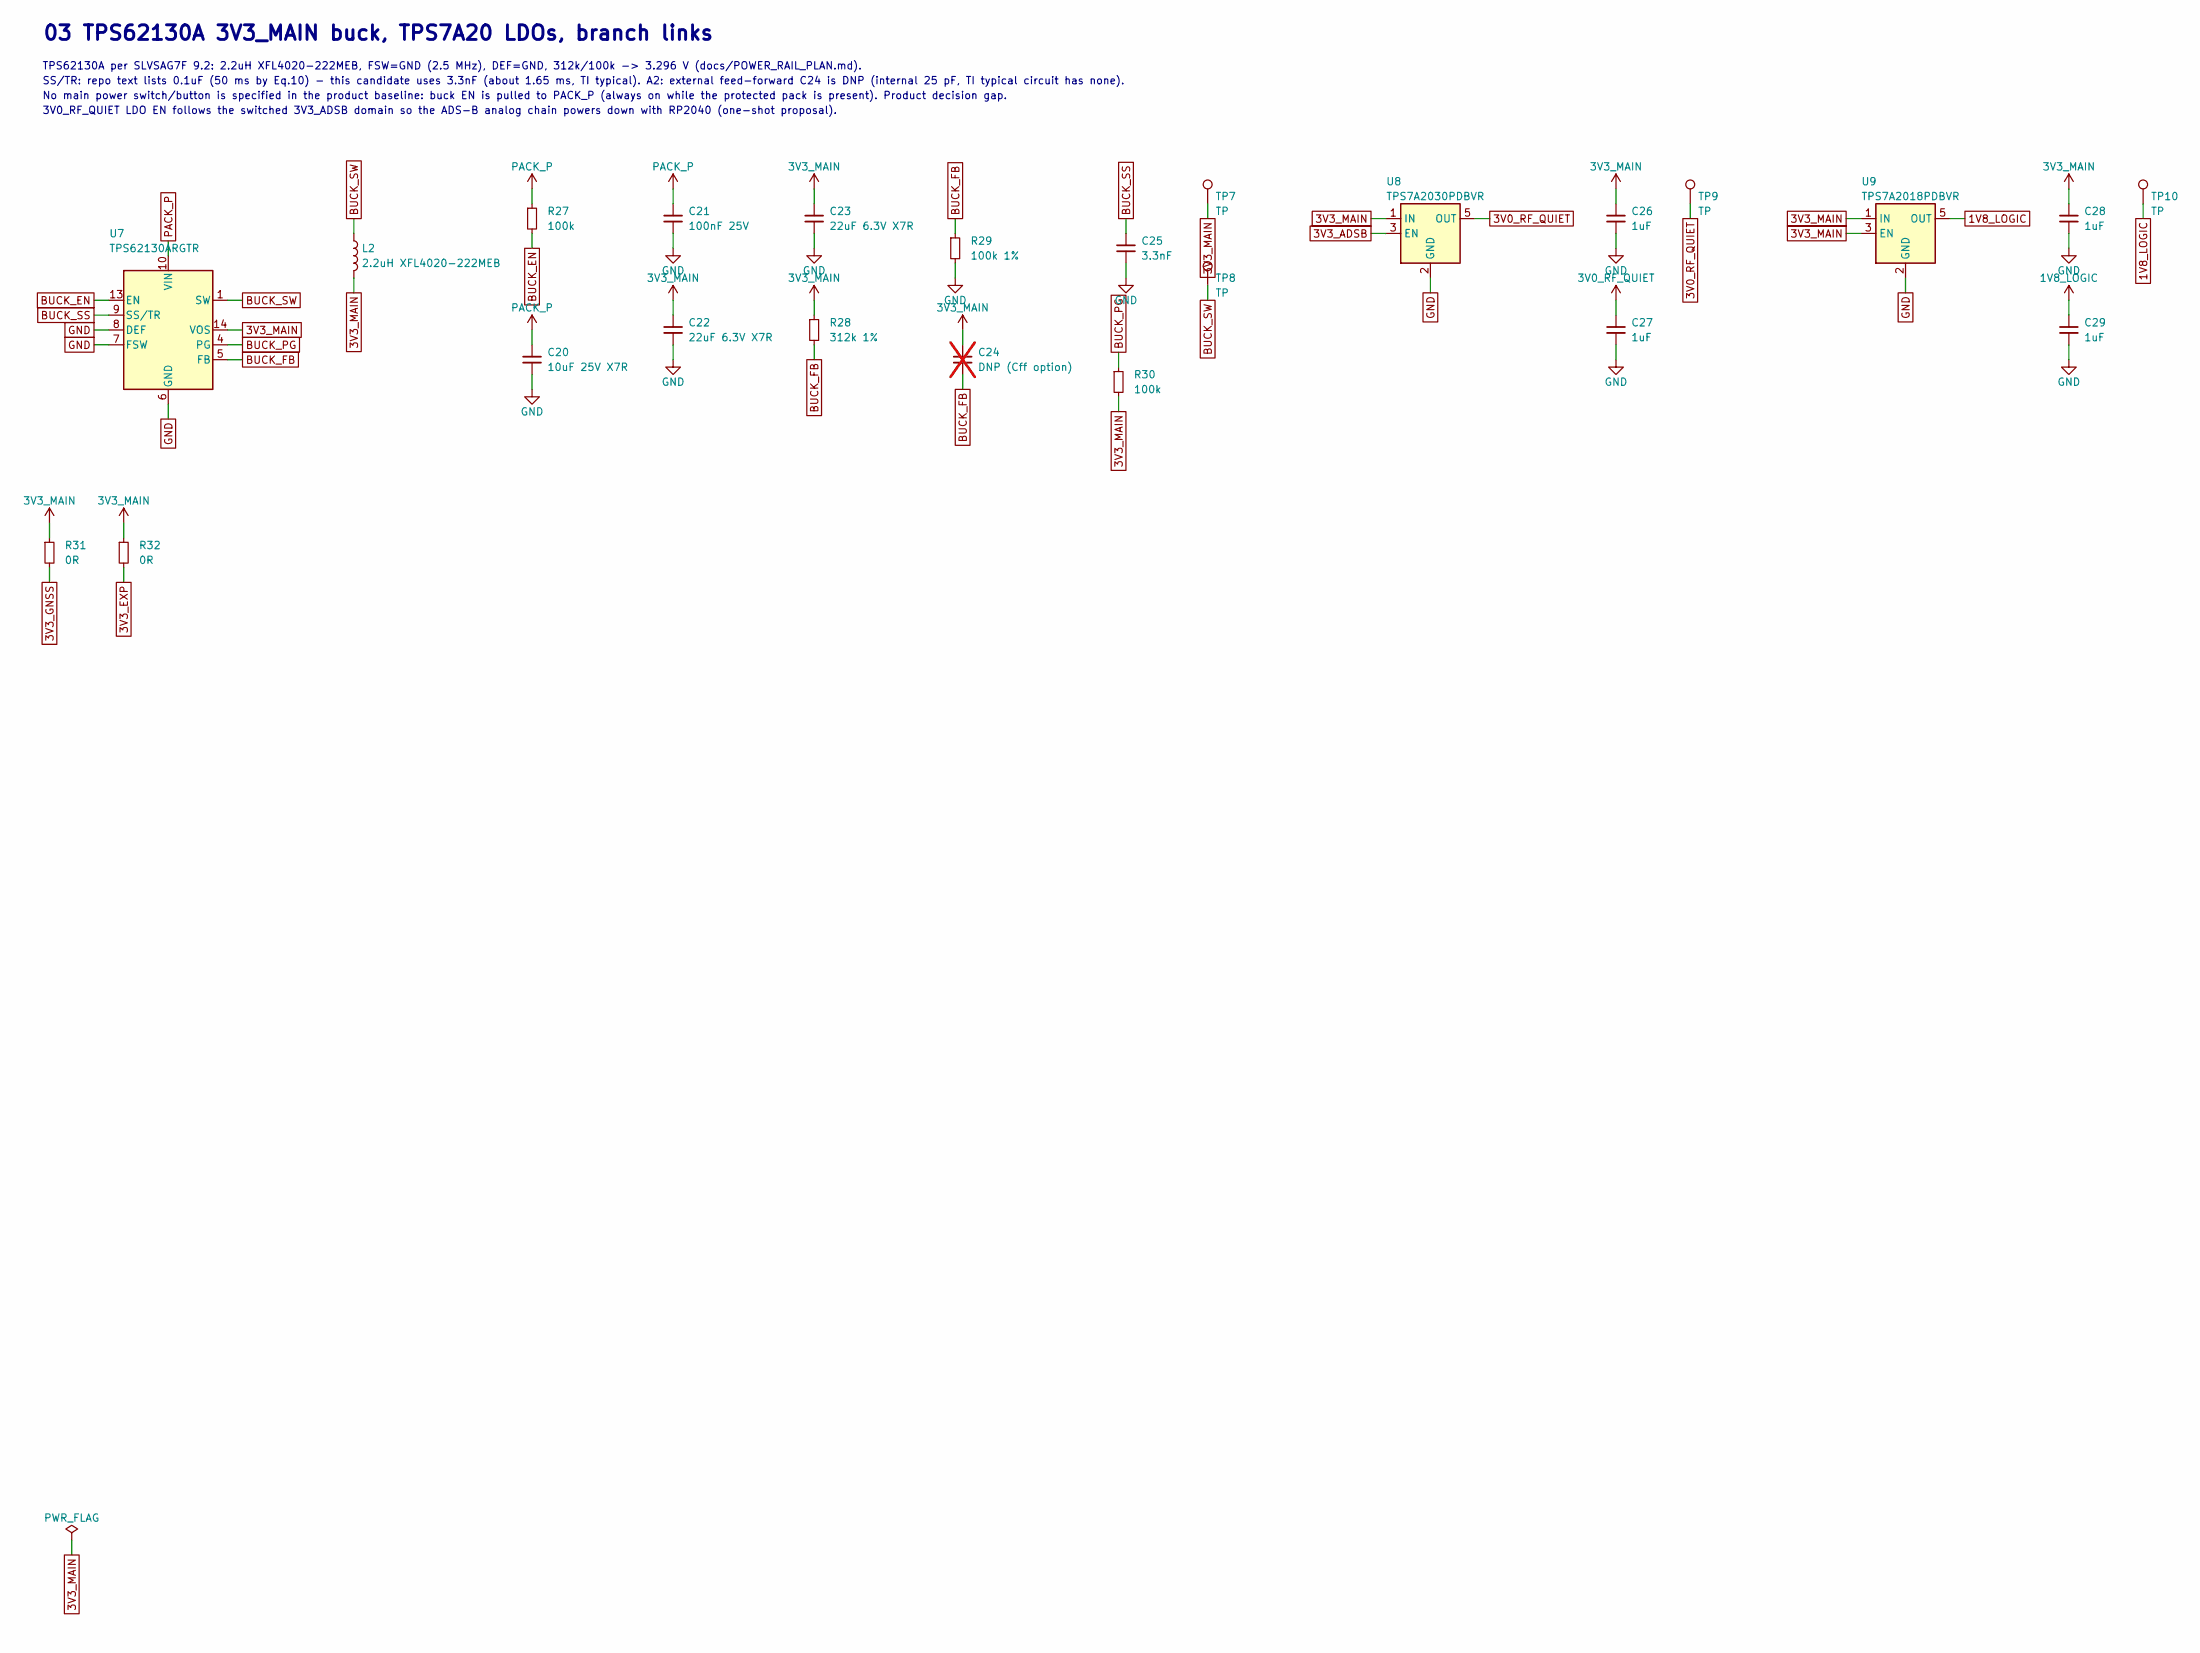
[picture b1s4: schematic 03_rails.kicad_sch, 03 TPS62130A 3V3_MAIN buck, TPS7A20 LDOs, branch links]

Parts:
C20: 10uF 25V X7R; C_0805_2012Metric
C21: 100nF 25V; C_0402_1005Metric
C22, C23: 22uF 6.3V X7R; C_0805_2012Metric
C24: DNP (Cff option); C_0402_1005Metric; not fitted
C25: 3.3nF; C_0402_1005Metric
C26, C27, C28, C29: 1uF; C_0402_1005Metric
L2: 2.2uH XFL4020-222MEB; L_Coilcraft_XxL4020; MPN XFL4020-222MEB
R27, R30: 100k; R_0402_1005Metric
R28: 312k 1%; R_0402_1005Metric
R29: 100k 1%; R_0402_1005Metric
R31, R32: 0R; R_0603_1608Metric
TP7, TP8, TP9, TP10: TP; TestPoint_Pad_D1.0mm
U7: TPS62130ARGTR; TI_RGT0016C_VQFN-16_3x3mm_EP1.68x1.68_TPS62130A; MPN TPS62130ARGTR
U8: TPS7A2030PDBVR; TI_DBV0005A_SOT-23-5_TPS7A20; MPN TPS7A2030PDBVR
U9: TPS7A2018PDBVR; TI_DBV0005A_SOT-23-5_TPS7A20; MPN TPS7A2018PDBVR

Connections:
1V8_LOGIC: C29.1, TP10.1, U9.5 (OUT); also elsewhere on the board
3V0_RF_QUIET: C27.1, TP9.1, U8.5 (OUT); also elsewhere on the board
3V3_ADSB: U8.3 (EN); also elsewhere on the board
3V3_EXP: R32.2; also elsewhere on the board
3V3_GNSS: R31.2; also elsewhere on the board
3V3_MAIN: C22.1, C23.1, C24.1, C26.1, C28.1, L2.2, R28.1, R30.2, R31.1, R32.1, TP7.1, U7.14 (VOS), U8.1 (IN), U9.1 (IN), U9.3 (EN); also elsewhere on the board
BUCK_EN: R27.2, U7.13 (EN)
BUCK_FB: C24.2, R28.2, R29.1, U7.5 (FB)
BUCK_PG: R30.1, U7.4 (PG); also elsewhere on the board
BUCK_SS: C25.1, U7.9 (SS/TR)
BUCK_SW: L2.1, TP8.1, U7.1 (SW), U7.2 (SW), U7.3 (SW)
GND: C20.2, C21.2, C22.2, C23.2, C25.2, C26.2, C27.2, C28.2, C29.2, R29.2, U7.6 (GND), U7.7 (FSW), U7.8 (DEF), U7.15 (GND), U7.16 (GND), U7.17 (GND), U8.2 (GND), U9.2 (GND); also elsewhere on the board
PACK_P: C20.1, C21.1, R27.1, U7.10 (VIN), U7.11 (VIN), U7.12 (VIN); also elsewhere on the board

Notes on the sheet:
03 TPS62130A 3V3_MAIN buck, TPS7A20 LDOs, branch links
TPS62130A per SLVSAG7F 9.2: 2.2uH XFL4020-222MEB, FSW=GND (2.5 MHz), DEF=GND, 312k/100k -> 3.296 V (docs/POWER_RAIL_PLAN.md).
SS/TR: repo text lists 0.1uF (50 ms by Eq.10) - this candidate uses 3.3nF (about 1.65 ms, TI typical). A2: external feed-forward C24 is DNP (internal 25 pF, TI typical circuit has none).
No main power switch/button is specified in the product baseline: buck EN is pulled to PACK_P (always on while the protected pack is present). Product decision gap.
3V0_RF_QUIET LDO EN follows the switched 3V3_ADSB domain so the ADS-B analog chain powers down with RP2040 (one-shot proposal).
